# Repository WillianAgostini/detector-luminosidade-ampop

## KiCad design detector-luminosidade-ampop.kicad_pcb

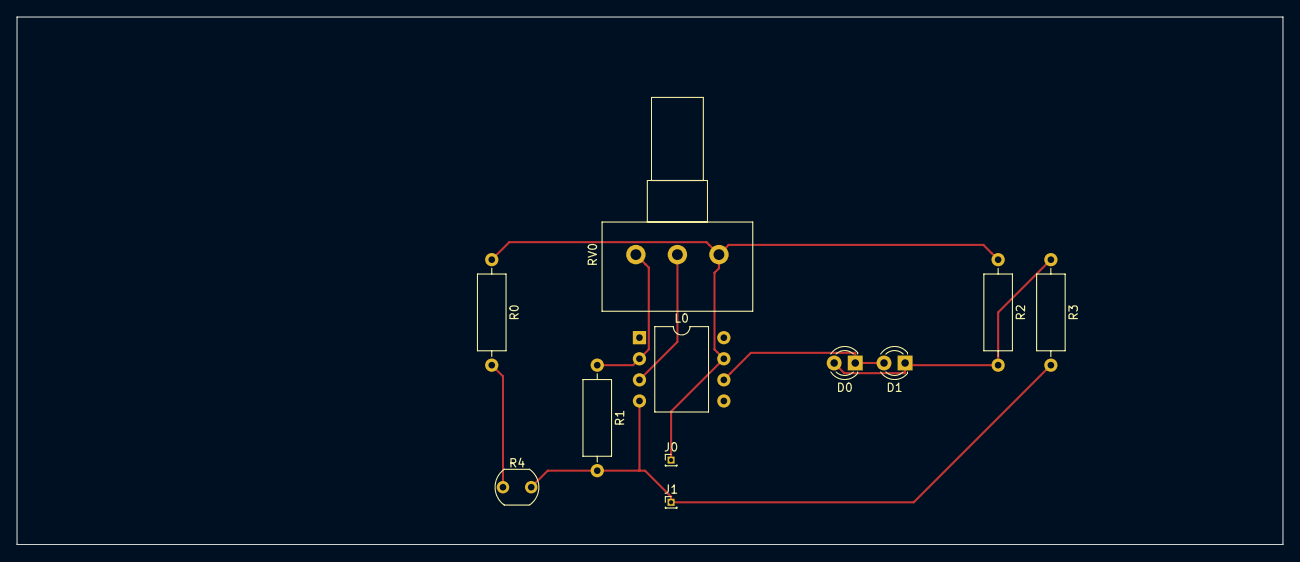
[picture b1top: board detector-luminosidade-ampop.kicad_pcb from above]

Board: 2 copper layers, 152.4 x 63.5 mm, 11 parts (0 on the bottom side), 7 nets.

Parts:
D0, D1: LED; LED_D3.0mm
J0, J1: Conn_01x01_Male; PinHeader_1x01_P1.00mm_Vertical
L0: LM741; DIP-8_W10.16mm
R0, R1, R2, R3: R; R_Axial_DIN0309_L9.0mm_D3.2mm_P12.70mm_Horizontal
R4: LDR07; R_LDR_5.1x4.3mm_P3.4mm_Vertical
RV0: R_POT; Potentiometer_Alps_RK163_Single_Horizontal

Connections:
unnamed: D0.1, D1.2, L0.6
unnamed: D0.2, D1.1, R2.2, R3.1
unnamed: J0.1, L0.7, R0.1, R2.1, RV0.1
unnamed: J1.1, L0.4, R1.2, R3.2, R4.2
unnamed: L0.2, R1.1, RV0.3
unnamed: L0.3, RV0.2
unnamed: R0.2, R4.1
